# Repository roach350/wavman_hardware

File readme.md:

# WAVMAN Hardware
## WAVMAN Overview
WAVMAN is an open source portable PCM audio player based around the ATSAMD21 serieis of microcontrollers and the PCM5102 DAC. It supports SD via an SPI interface.

## Revisions and Notes
### REV 0
- Wrong symbol for USB-C resulting in only one pair of DP/DM being connected
- DAC does not have 3.3v on VDDIO or VDDIN
- PCM_MUTE (DAC mute) is not connected to MCU or even a pull up resistor to 3.3v so DAC is always muted by default
- The hold switch was botched (not connected to MCU and wrong net for power)
- All displays sink current from the LDO instaed of the battery directly, it may be desirable to change this
- No dedicated debug port for SWCLK and SWDIO
- The audio amp. has is missing several compontents (feedback resistors Rf and decoupling cap.)
- AMP_SHUTDOWN is not connected to the MCU
### REV 1
- should fix all major issues with REV 0
- minor tweaks to switch and knob placement
- 0805 passive components
- rerouted audio ICs
- knockout silkscreen for userfacing text

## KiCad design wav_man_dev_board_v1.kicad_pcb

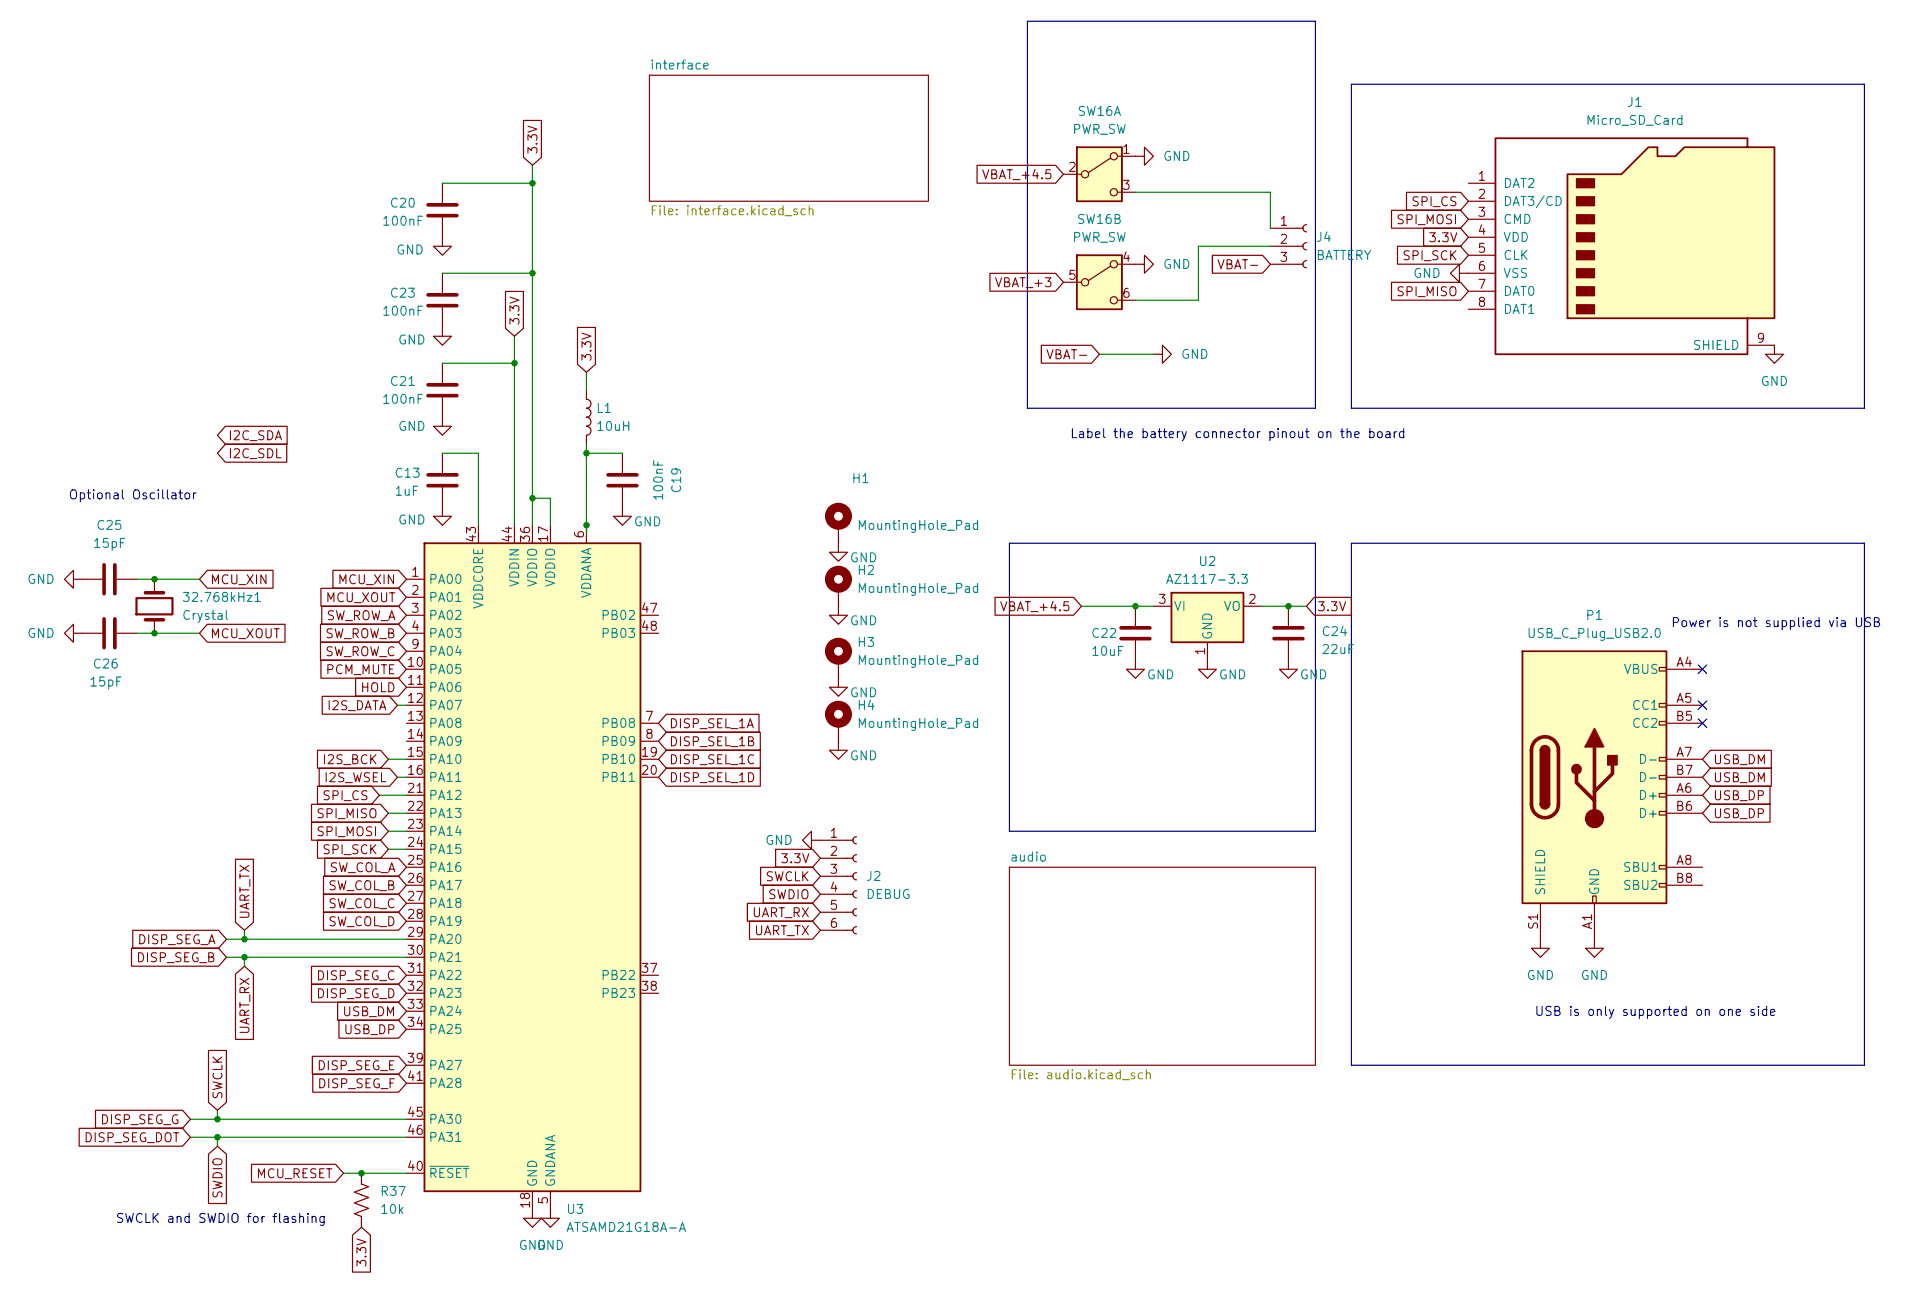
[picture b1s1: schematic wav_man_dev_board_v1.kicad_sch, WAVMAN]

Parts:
32.768kHz1: Crystal; Crystal_HC49-U_Vertical
C13: 1uF; C_0805_2012Metric_Pad1.18x1.45mm_HandSolder
C19, C20, C21, C23: 100nF; C_0805_2012Metric_Pad1.18x1.45mm_HandSolder
C22: 10uF; C_0805_2012Metric_Pad1.18x1.45mm_HandSolder
C24: 22uF; C_0805_2012Metric_Pad1.18x1.45mm_HandSolder
C25, C26: 15pF; C_0805_2012Metric_Pad1.18x1.45mm_HandSolder
H1, H2, H3, H4: MountingHole_Pad; MountingHole_2.7mm_M2.5_DIN965_Pad
J1: Micro_SD_Card; microSD_HC_Molex_47219-2001
J2: DEBUG; PinSocket_1x06_P2.54mm_Vertical
J4: BATTERY; JST_PH_B3B-PH-K_1x03_P2.00mm_Vertical
L1: 10uH; L_0805_2012Metric_Pad1.15x1.40mm_HandSolder
P1: USB_C_Plug_USB2.0; USB_C_Receptacle_GCT_USB4105-xx-A_16P_TopMnt_Horizontal
R37: 10k; R_0805_2012Metric_Pad1.20x1.40mm_HandSolder
SW16: PWR_SW; SW_E-Switch_EG2219_DPDT_Angled
U2: AZ1117-3.3; SOT-223-3_TabPin2
U3: ATSAMD21G18A-A; TQFP-48_7x7mm_P0.5mm

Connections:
3.3V: C20.1, C21.1, C23.1, C24.1, J1.4 (VDD), J2.2, L1.1, R37.2, U2.2 (VO), U3.17 (VDDIO), U3.36 (VDDIO), U3.44 (VDDIN); also elsewhere on the board
DISP_SEG_A: J2.6, U3.29 (PA20); also elsewhere on the board
DISP_SEG_B: J2.5, U3.30 (PA21); also elsewhere on the board
DISP_SEG_C: U3.31 (PA22); also elsewhere on the board
DISP_SEG_D: U3.32 (PA23); also elsewhere on the board
DISP_SEG_DOT: J2.4, U3.46 (PA31); also elsewhere on the board
DISP_SEG_E: U3.39 (PA27); also elsewhere on the board
DISP_SEG_F: U3.41 (PA28); also elsewhere on the board
DISP_SEG_G: J2.3, U3.45 (PA30); also elsewhere on the board
DISP_SEL_1A: U3.7 (PB08); also elsewhere on the board
DISP_SEL_1B: U3.8 (PB09); also elsewhere on the board
DISP_SEL_1C: U3.19 (PB10); also elsewhere on the board
DISP_SEL_1D: U3.20 (PB11); also elsewhere on the board
HOLD: U3.11 (PA06); also elsewhere on the board
I2S_BCK: U3.15 (PA10); also elsewhere on the board
I2S_DATA: U3.12 (PA07); also elsewhere on the board
I2S_WSEL: U3.16 (PA11); also elsewhere on the board
MCU_RESET: R37.1, U3.40 (~RESET); also elsewhere on the board
MCU_XIN: 32.768kHz1.2, C25.2, U3.1 (PA00); also elsewhere on the board
MCU_XOUT: 32.768kHz1.1, C26.2, U3.2 (PA01); also elsewhere on the board
unnamed: J4.1, SW16.3 (C)
unnamed: J4.2, SW16.6 (C)
unnamed: C19.1, L1.2, U3.6 (VDDANA)
unnamed: C13.2, U3.43 (VDDCORE)
PCM_MUTE: U3.10 (PA05); also elsewhere on the board
SPI_CS: J1.2 (DAT3/CD), U3.21 (PA12)
SPI_MISO: J1.7 (DAT0), U3.22 (PA13)
SPI_MOSI: J1.3 (CMD), U3.23 (PA14)
SPI_SCK: J1.5 (CLK), U3.24 (PA15)
SW_COL_A: U3.25 (PA16); also elsewhere on the board
SW_COL_B: U3.26 (PA17); also elsewhere on the board
SW_COL_C: U3.27 (PA18); also elsewhere on the board
SW_COL_D: U3.28 (PA19); also elsewhere on the board
SW_ROW_A: U3.3 (PA02); also elsewhere on the board
SW_ROW_B: U3.4 (PA03); also elsewhere on the board
SW_ROW_C: U3.9 (PA04); also elsewhere on the board
USB_DM: P1.A7 (D-), P1.B7 (D-), U3.33 (PA24)
USB_DP: P1.A6 (D+), P1.B6 (D+), U3.34 (PA25)
VBAT-: C13.1, C19.2, C20.2, C21.2, C22.2, C23.2, C24.2, C25.1, C26.1, H1.1, H2.1, H3.1, H4.1, J1.6 (VSS), J1.9 (SHIELD), J2.1, J4.3, P1.A1 (GND), P1.A12 (GND), P1.B1 (GND), P1.B12 (GND), P1.S1 (SHIELD), SW16.1 (A), SW16.4 (A), U2.1 (GND), U3.5 (GNDANA), U3.18 (GND), U3.35 (GND), U3.42 (GND); also elsewhere on the board
VBAT_+3: SW16.5 (B)
VBAT_+4.5: C22.1, SW16.2 (B), U2.3 (VI)

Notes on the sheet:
Power is not supplied via USB
SWCLK and SWDIO for flashing
Label the battery connector pinout on the board
USB is only supported on one side
Optional Oscillator

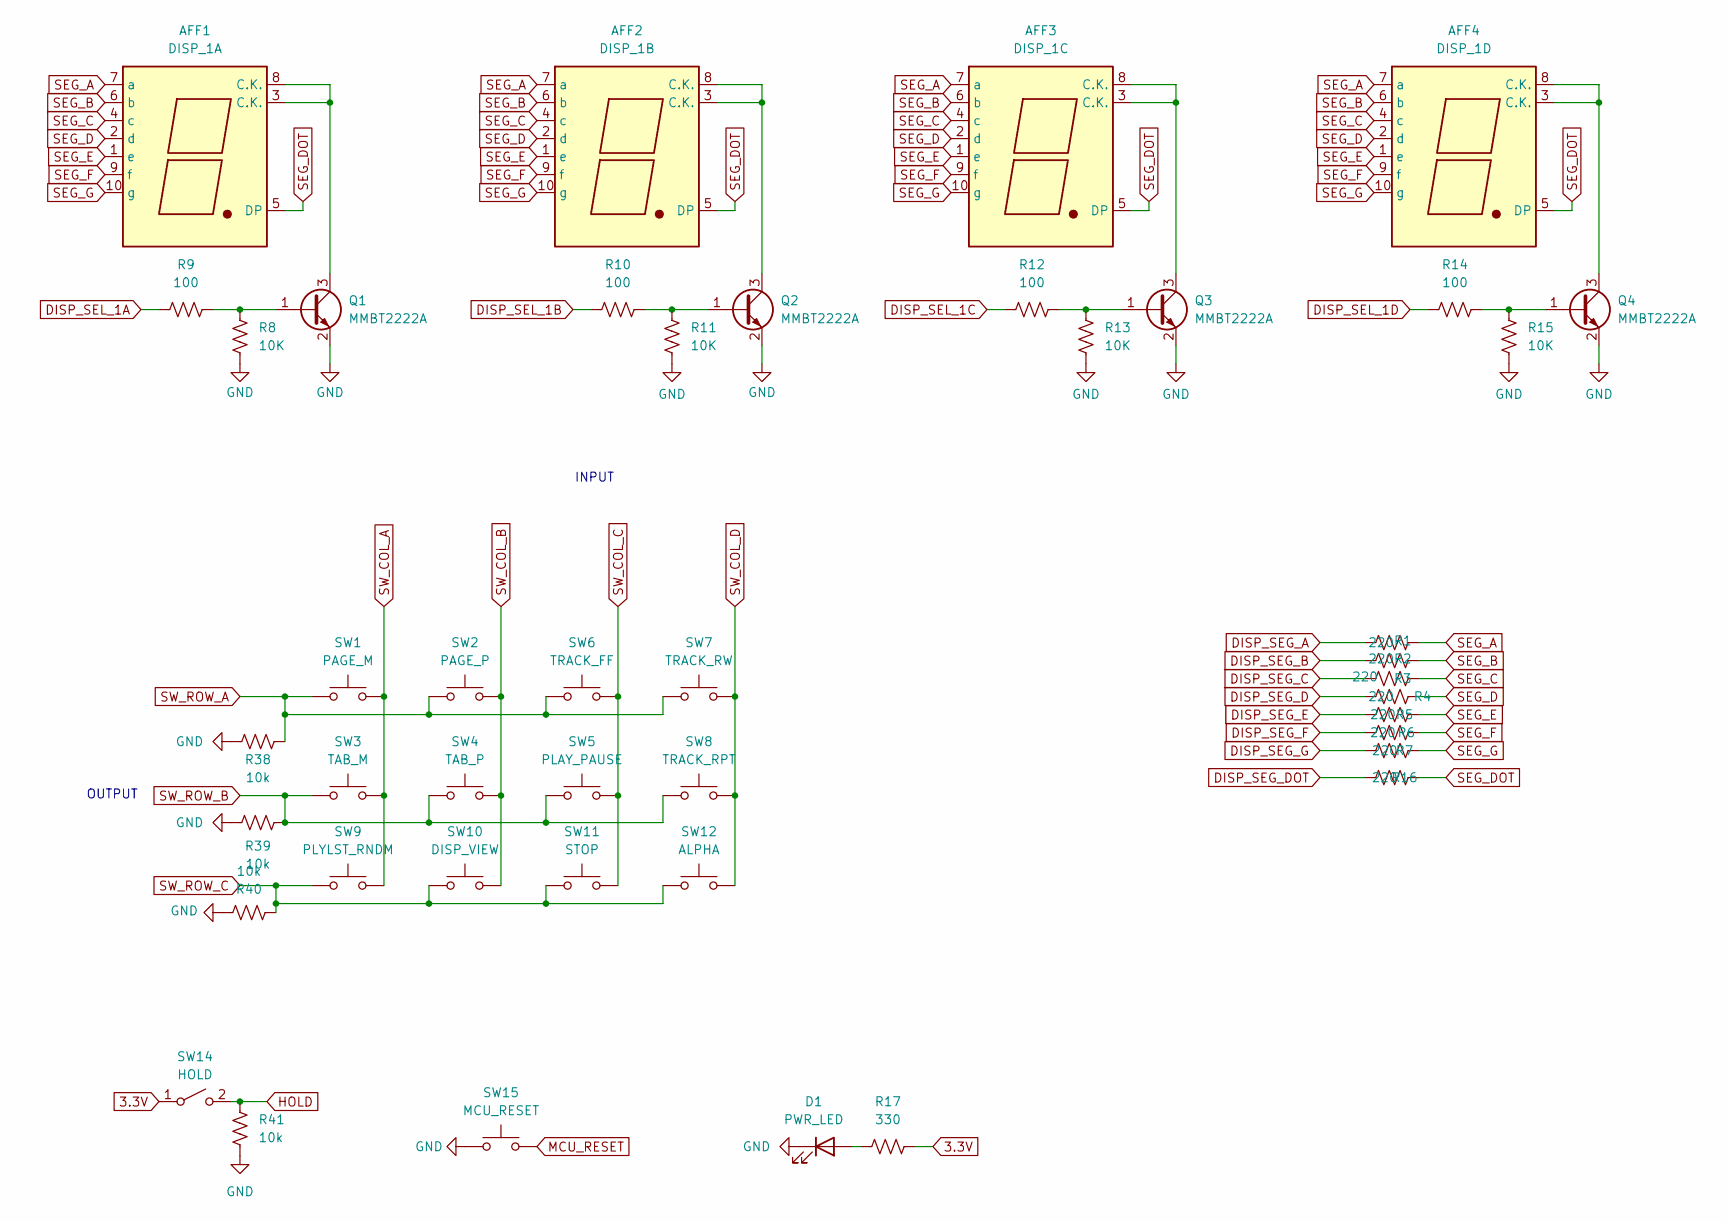
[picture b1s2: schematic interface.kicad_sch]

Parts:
AFF1: DISP_1A; 7SegmentLED_LTS6760_LTS6780
AFF2: DISP_1B; 7SegmentLED_LTS6760_LTS6780
AFF3: DISP_1C; 7SegmentLED_LTS6760_LTS6780
AFF4: DISP_1D; 7SegmentLED_LTS6760_LTS6780
D1: PWR_LED; LED_1206_3216Metric_Pad1.42x1.75mm_HandSolder
Q1, Q2, Q3, Q4: MMBT2222A; SOT-23_Handsoldering
R1, R2, R3, R4, R5, R6, R7, R16: 220; R_0805_2012Metric_Pad1.20x1.40mm_HandSolder
R8, R11, R13, R15: 10K; R_0805_2012Metric_Pad1.20x1.40mm_HandSolder
R9, R10, R12, R14: 100; R_0805_2012Metric_Pad1.20x1.40mm_HandSolder
R17: 330; R_0805_2012Metric_Pad1.20x1.40mm_HandSolder
R38, R39, R40, R41: 10k; R_0805_2012Metric_Pad1.20x1.40mm_HandSolder
SW1: PAGE_M; SW_PUSH_6mm
SW2: PAGE_P; SW_PUSH_6mm
SW3: TAB_M; SW_PUSH_6mm
SW4: TAB_P; SW_PUSH_6mm
SW5: PLAY_PAUSE; SW_PUSH_6mm
SW6: TRACK_FF; SW_PUSH_6mm
SW7: TRACK_RW; SW_PUSH_6mm
SW8: TRACK_RPT; SW_PUSH_6mm
SW9: PLYLST_RNDM; SW_PUSH_6mm
SW10: DISP_VIEW; SW_PUSH_6mm
SW11: STOP; SW_PUSH_6mm
SW12: ALPHA; SW_PUSH_6mm
SW14: HOLD; SW_Slide_SPDT_Angled_CK_OS102011MA1Q
SW15: MCU_RESET; SW_PUSH_6mm

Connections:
3.3V: R17.2, SW14.1 (A); also elsewhere on the board
DISP_SEG_A: R1.1; also elsewhere on the board
DISP_SEG_B: R2.1; also elsewhere on the board
DISP_SEG_C: R3.1; also elsewhere on the board
DISP_SEG_D: R4.1; also elsewhere on the board
DISP_SEG_DOT: R16.1; also elsewhere on the board
DISP_SEG_E: R5.1; also elsewhere on the board
DISP_SEG_F: R6.1; also elsewhere on the board
DISP_SEG_G: R7.1; also elsewhere on the board
DISP_SEL_1A: R9.1; also elsewhere on the board
DISP_SEL_1B: R10.1; also elsewhere on the board
DISP_SEL_1C: R12.1; also elsewhere on the board
DISP_SEL_1D: R14.1; also elsewhere on the board
HOLD: R41.1, SW14.2 (B); also elsewhere on the board
MCU_RESET: SW15.2; also elsewhere on the board
unnamed: D1.2 (A), R17.1
unnamed: Q1.1 (B), R8.1, R9.2
unnamed: AFF1.3 (C.K.), AFF1.8 (C.K.), Q1.3 (C)
unnamed: Q2.1 (B), R10.2, R11.1
unnamed: AFF2.3 (C.K.), AFF2.8 (C.K.), Q2.3 (C)
unnamed: Q3.1 (B), R12.2, R13.1
unnamed: AFF3.3 (C.K.), AFF3.8 (C.K.), Q3.3 (C)
unnamed: Q4.1 (B), R14.2, R15.1
unnamed: AFF4.3 (C.K.), AFF4.8 (C.K.), Q4.3 (C)
SEG_A: AFF1.7 (a), AFF2.7 (a), AFF3.7 (a), AFF4.7 (a), R1.2
SEG_B: AFF1.6 (b), AFF2.6 (b), AFF3.6 (b), AFF4.6 (b), R2.2
SEG_C: AFF1.4 (c), AFF2.4 (c), AFF3.4 (c), AFF4.4 (c), R3.2
SEG_D: AFF1.2 (d), AFF2.2 (d), AFF3.2 (d), AFF4.2 (d), R4.2
SEG_DOT: AFF1.5 (DP), AFF2.5 (DP), AFF3.5 (DP), AFF4.5 (DP), R16.2
SEG_E: AFF1.1 (e), AFF2.1 (e), AFF3.1 (e), AFF4.1 (e), R5.2
SEG_F: AFF1.9 (f), AFF2.9 (f), AFF3.9 (f), AFF4.9 (f), R6.2
SEG_G: AFF1.10 (g), AFF2.10 (g), AFF3.10 (g), AFF4.10 (g), R7.2
SW_COL_A: SW1.2, SW3.2, SW9.2; also elsewhere on the board
SW_COL_B: SW2.2, SW4.2, SW10.2; also elsewhere on the board
SW_COL_C: SW5.2, SW6.2, SW11.2; also elsewhere on the board
SW_COL_D: SW7.2, SW8.2, SW12.2; also elsewhere on the board
SW_ROW_A: R38.2, SW1.1, SW2.1, SW6.1, SW7.1; also elsewhere on the board
SW_ROW_B: R39.2, SW3.1, SW4.1, SW5.1, SW8.1; also elsewhere on the board
SW_ROW_C: R40.2, SW9.1, SW10.1, SW11.1, SW12.1; also elsewhere on the board
VBAT-: D1.1 (K), Q1.2 (E), Q2.2 (E), Q3.2 (E), Q4.2 (E), R8.2, R11.2, R13.2, R15.2, R38.1, R39.1, R40.1, R41.2, SW15.1; also elsewhere on the board

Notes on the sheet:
OUTPUT
INPUT

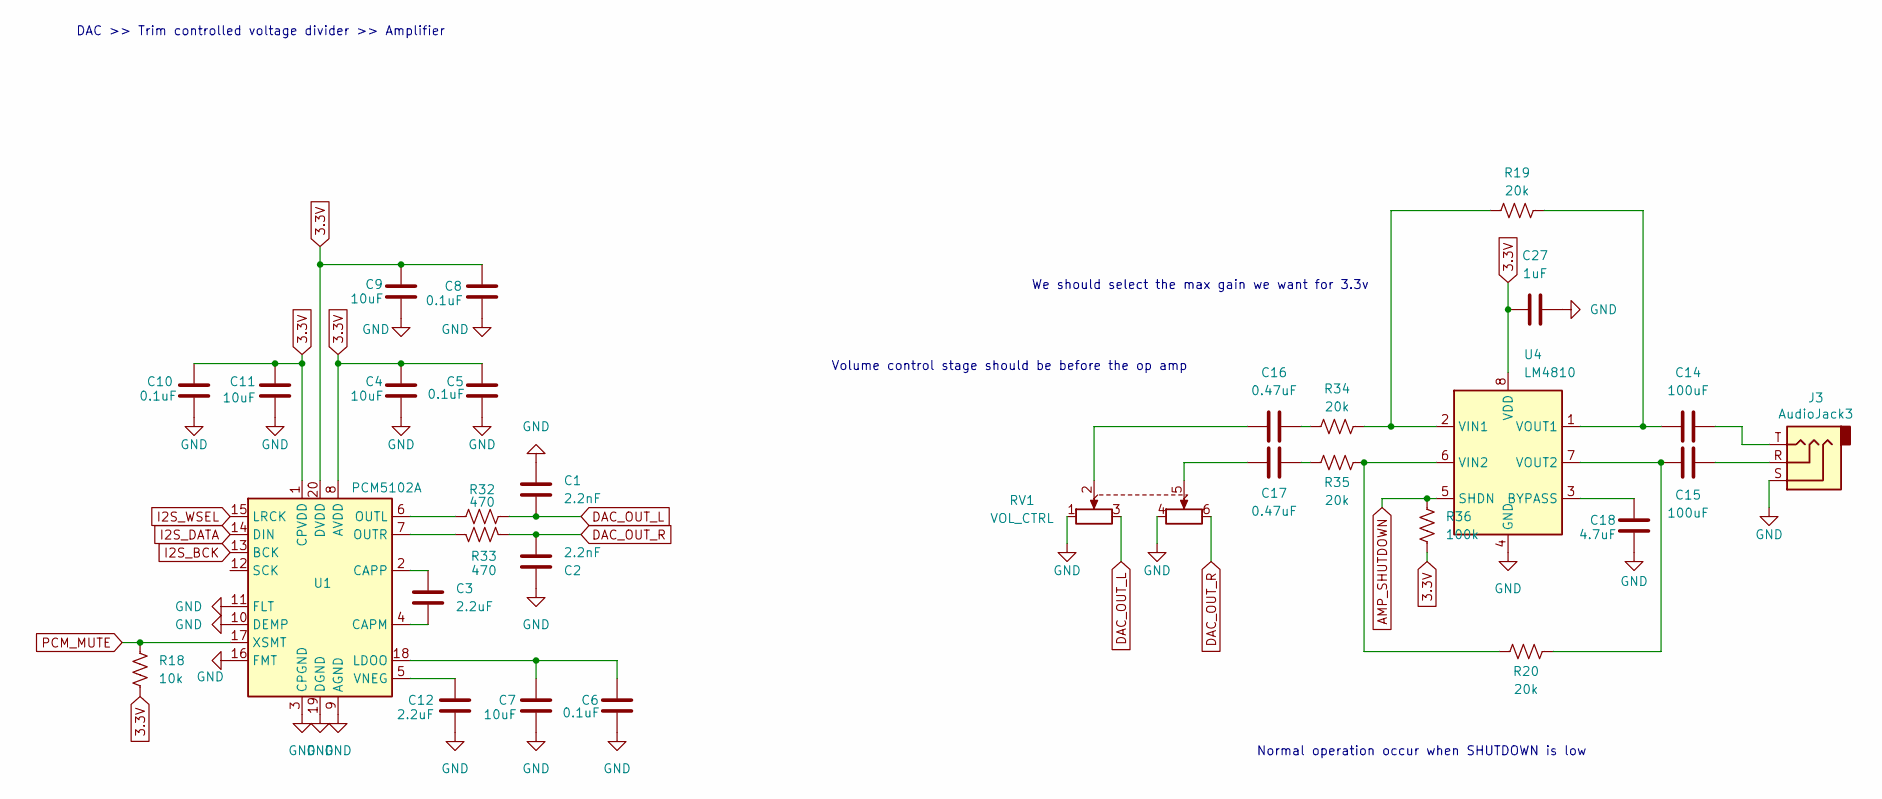
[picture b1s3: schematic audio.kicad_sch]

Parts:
C1, C2: 2.2nF; C_0805_2012Metric_Pad1.18x1.45mm_HandSolder
C3, C12: 2.2uF; C_0805_2012Metric_Pad1.18x1.45mm_HandSolder
C4, C7, C9, C11: 10uF; C_0805_2012Metric_Pad1.18x1.45mm_HandSolder
C5, C6, C8, C10: 0.1uF; C_0805_2012Metric_Pad1.18x1.45mm_HandSolder
C14, C15: 100uF; C_1206_3216Metric_Pad1.33x1.80mm_HandSolder
C16, C17: 0.47uF; C_0805_2012Metric_Pad1.18x1.45mm_HandSolder
C18: 4.7uF; C_0805_2012Metric_Pad1.18x1.45mm_HandSolder
C27: 1uF; C_0805_2012Metric_Pad1.18x1.45mm_HandSolder
J3: AudioJack3; Jack_3.5mm_CUI_SJ1-3533NG_Horizontal
R18: 10k; R_0805_2012Metric_Pad1.20x1.40mm_HandSolder
R19, R20, R34, R35: 20k; R_0805_2012Metric_Pad1.20x1.40mm_HandSolder
R32, R33: 470; R_0805_2012Metric_Pad1.20x1.40mm_HandSolder
R36: 100k; R_0805_2012Metric_Pad1.20x1.40mm_HandSolder
RV1: VOL_CTRL; Potentiometer_Alps_RK097_Dual_Horizontal
U1: PCM5102A; TSSOP-20_4.4x6.5mm_P0.65mm
U4: LM4810; TSSOP-8_3x3mm_P0.65mm

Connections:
3.3V: C4.1, C5.1, C8.1, C9.1, C10.1, C11.1, C27.1, R18.2, R36.2, U1.1 (CPVDD), U1.8 (AVDD), U1.20 (DVDD), U4.8 (VDD); also elsewhere on the board
AMP_SHUTDOWN: R36.1, U4.5 (SHDN)
DAC_OUT_L: C1.2, R32.2, RV1.3
DAC_OUT_R: C2.2, R33.2, RV1.6
I2S_BCK: U1.13 (BCK); also elsewhere on the board
I2S_DATA: U1.14 (DIN); also elsewhere on the board
I2S_WSEL: U1.15 (LRCK); also elsewhere on the board
unnamed: C14.2, J3.T
unnamed: C15.2, J3.R
unnamed: C16.1, RV1.2
unnamed: C16.2, R34.1
unnamed: C17.1, RV1.5
unnamed: C17.2, R35.1
unnamed: C3.2, U1.4 (CAPM)
unnamed: C3.1, U1.2 (CAPP)
unnamed: C6.1, C7.1, U1.18 (LDOO)
unnamed: R32.1, U1.6 (OUTL)
unnamed: R33.1, U1.7 (OUTR)
unnamed: C12.1, U1.5 (VNEG)
unnamed: C18.1, U4.3 (BYPASS)
unnamed: R19.1, R34.2, U4.2 (VIN1)
unnamed: R20.1, R35.2, U4.6 (VIN2)
unnamed: C14.1, R19.2, U4.1 (VOUT1)
unnamed: C15.1, R20.2, U4.7 (VOUT2)
PCM_MUTE: R18.1, U1.17 (XSMT); also elsewhere on the board
VBAT-: C1.1, C2.1, C4.2, C5.2, C6.2, C7.2, C8.2, C9.2, C10.2, C11.2, C12.2, C18.2, C27.2, J3.S, RV1.1, RV1.4, U1.3 (CPGND), U1.9 (AGND), U1.10 (DEMP), U1.11 (FLT), U1.16 (FMT), U1.19 (DGND), U4.4 (GND); also elsewhere on the board

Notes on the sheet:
Volume control stage should be before the op amp
We should select the max gain we want for 3.3v
Normal operation occur when SHUTDOWN is low
DAC >> Trim controlled voltage divider >> Amplifier

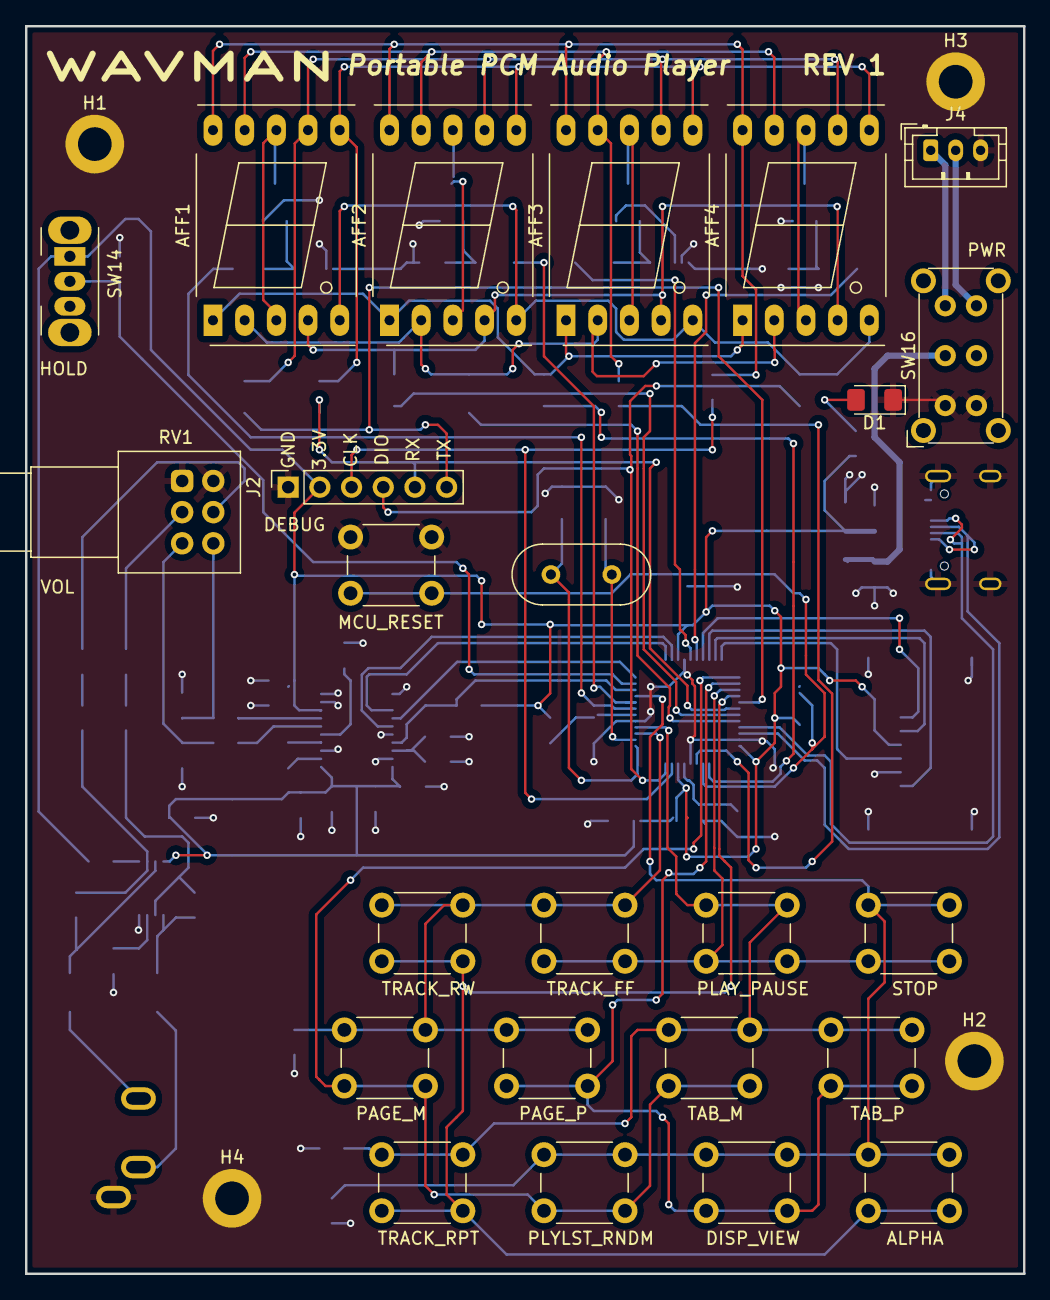
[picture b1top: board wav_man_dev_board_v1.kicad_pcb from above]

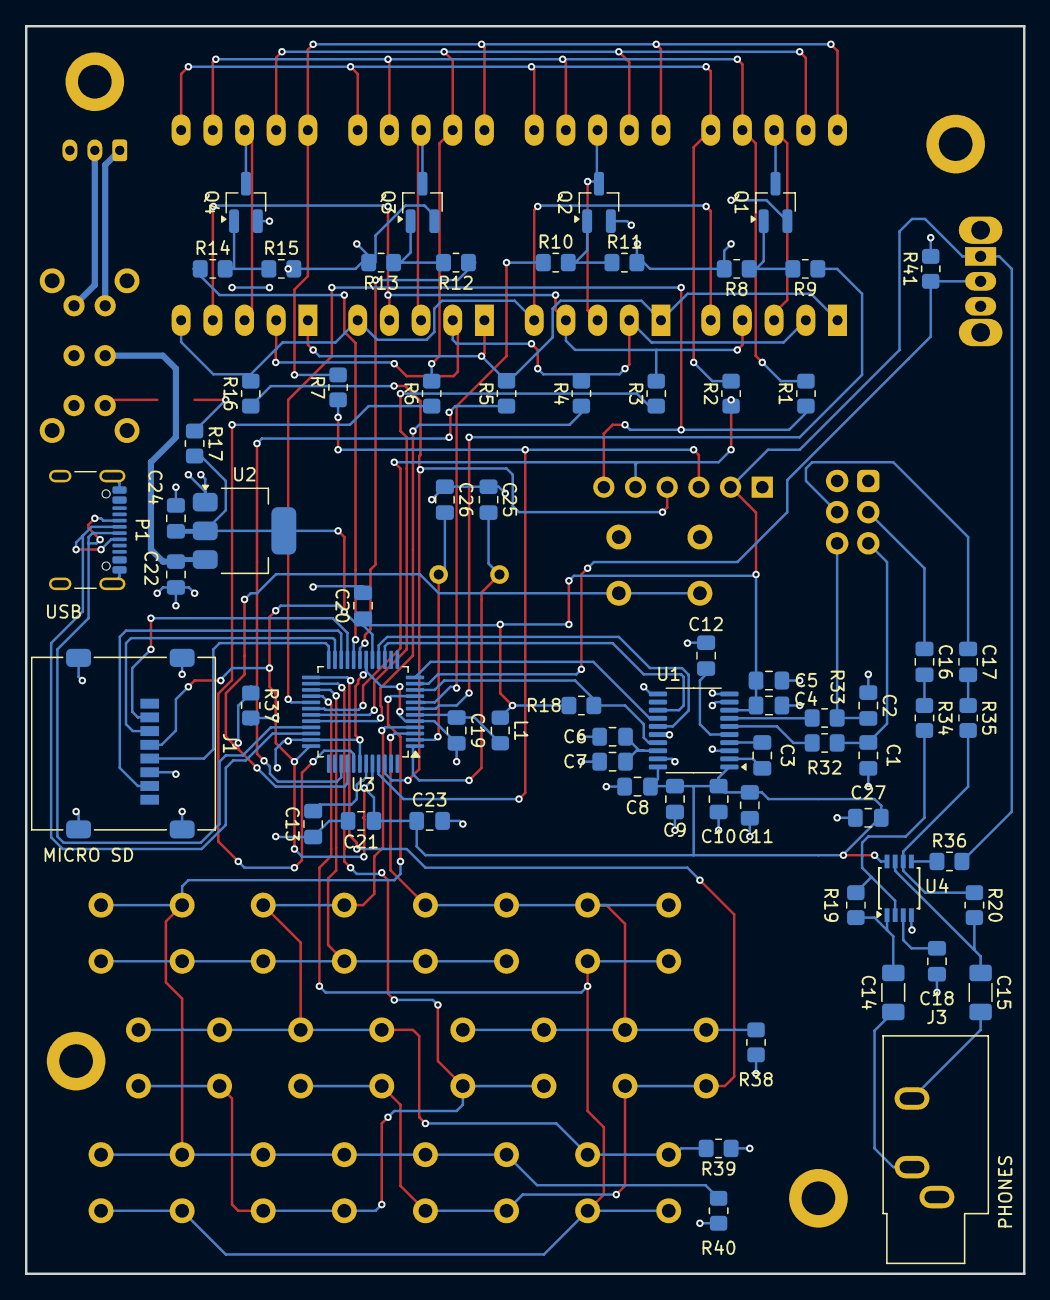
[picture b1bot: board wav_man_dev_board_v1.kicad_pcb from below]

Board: 2 copper layers, 80.0 x 100.0 mm, 97 parts (69 on the bottom side), 77 nets.

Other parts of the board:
32.768kHz: Crystal; Crystal_HC49-U_Vertical

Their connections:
MCU_XIN: 32.768kHz.2; also elsewhere on the board
MCU_XOUT: 32.768kHz.1; also elsewhere on the board
